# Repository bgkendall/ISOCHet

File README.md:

# ISOCHět

Macro pad based around an ISO Enter and using the CH552E MCU.

## Prerequisites

 * KiCad v7.0.9 or later
 * The following KiCad plugins are used for keyboard-specific components:
   * [marbastlib](https://github.com/ebastler/marbastlib) — footprints
   * [Keyswitch Kicad Library](https://github.com/kiswitch/kiswitch) —  3D models
 * [Josefin Sans](https://github.com/googlefonts/josefinsans) font — used for PCB text
 * FreeCAD v0.21.2 or later

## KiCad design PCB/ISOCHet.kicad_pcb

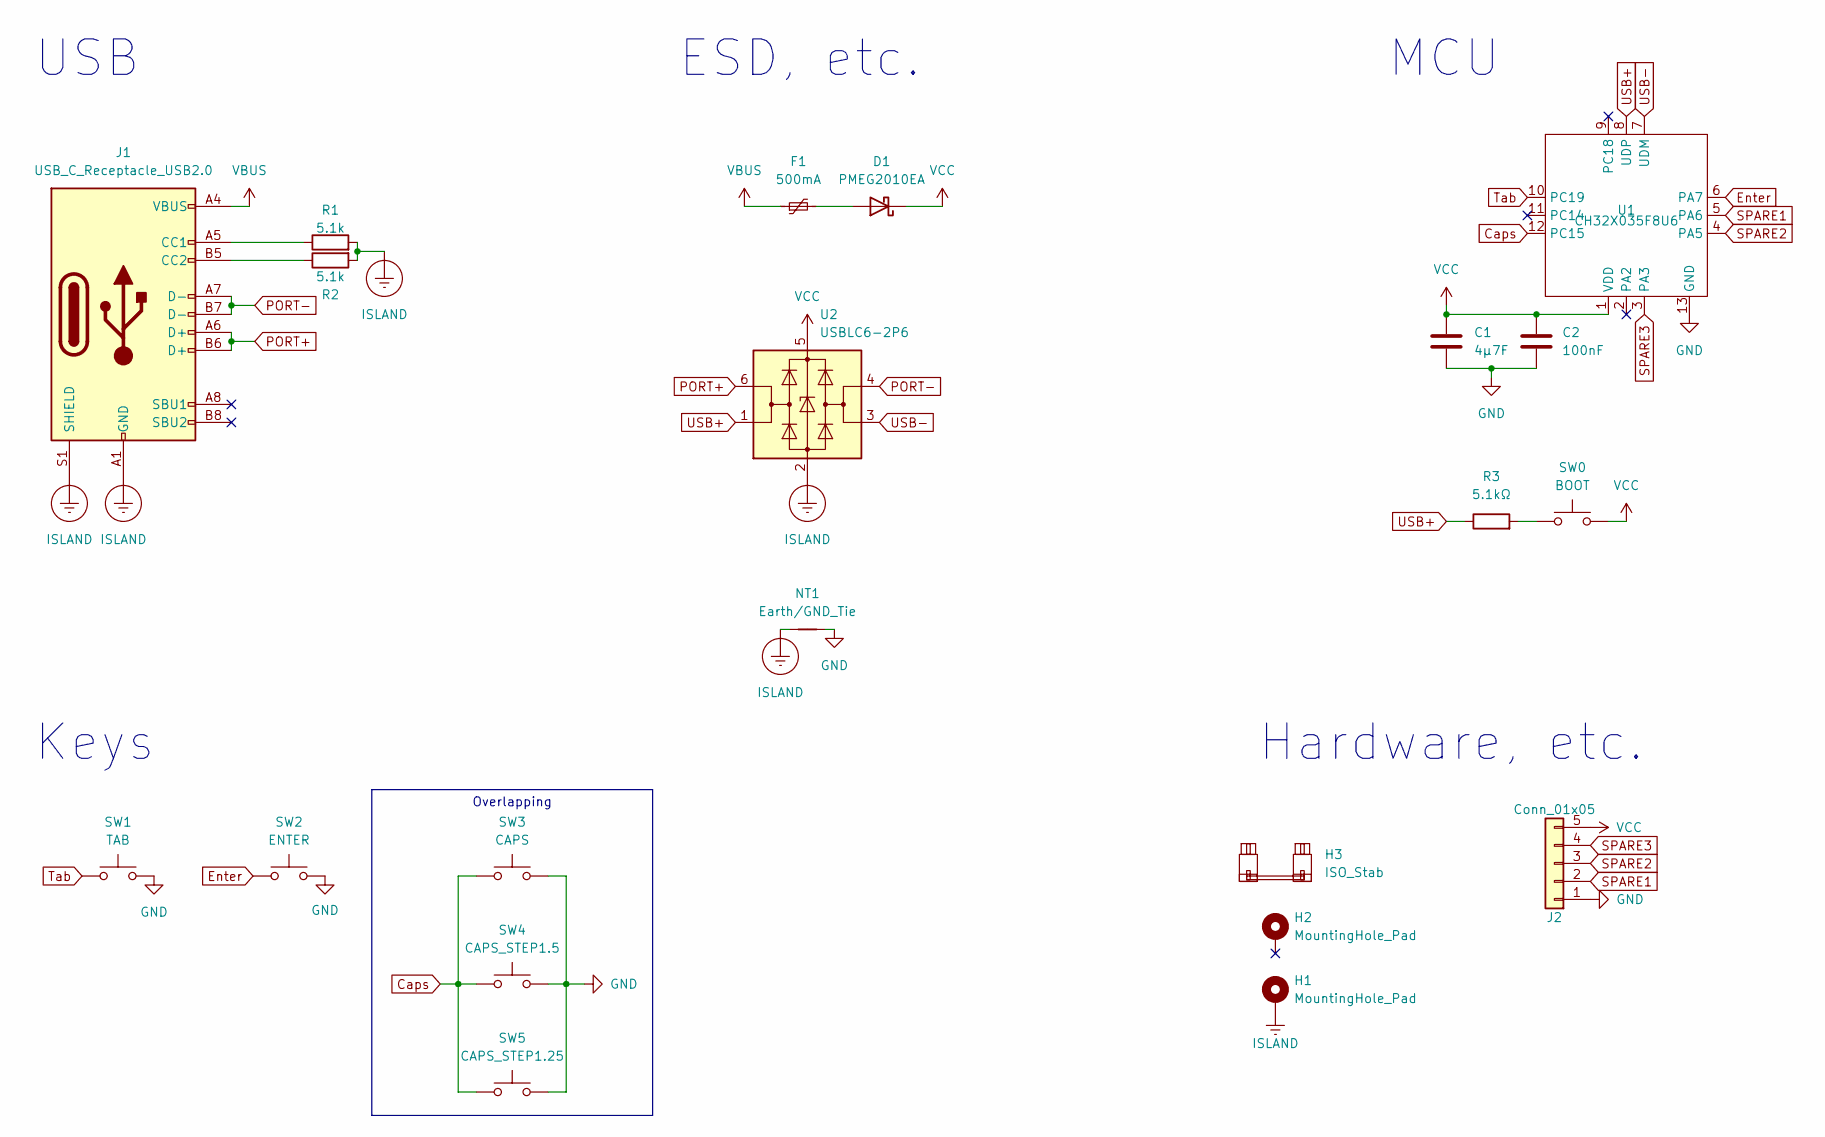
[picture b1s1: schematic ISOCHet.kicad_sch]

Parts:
C1: 4µ7F; C_0603_1608Metric_Pad1.08x0.95mm_HandSolder; LCSC C66501
C2: 100nF; C_0603_1608Metric_Pad1.08x0.95mm_HandSolder; LCSC C66501
D1: PMEG2010EA; D_SOD-323; LCSC C2837790
F1: 500mA; Fuse_0603_1608Metric_Pad1.05x0.95mm_HandSolder; LCSC C210357
H1, H2: MountingHole_Pad; MountingHole_2.2mm_M2_DIN965_Pad
H3: ISO_Stab; STAB_MX_P_ISO-ROT
J1: USB_C_Receptacle_USB2.0; GSB1C211110DS1HR; LCSC C2840393
J2: Conn_01x05; PinHeader_1x05_P2.00mm_Vertical
NT1: Earth/GND_Tie; NetTie_Via
R1, R2: 5.1k; R_0603_1608Metric_Pad0.98x0.95mm_HandSolder; LCSC C23186
R3: 5.1kΩ; R_0603_1608Metric_Pad0.98x0.95mm_HandSolder; LCSC C25804
SW0: BOOT; SW_SPST_SKQG_WithStem; LCSC C115351
SW1: TAB; SW_MX_1.5u
SW2: ENTER; SW_MX_1u
SW3: CAPS; SW_MX_1.75u
SW4: CAPS_STEP1.5; SW_MX_1.75u_STP_1.5
SW5: CAPS_STEP1.25; SW_MX_1.75u_STP_1.25
U1: CH32X035F8U6; UQFN-12-1EP_2x2mm_P0.4mm_EP1.1x1.1mm
U2: USBLC6-2P6; SOT-23-6_Handsoldering; LCSC C2827654

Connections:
Caps: SW3.1, SW4.1, SW5.1, U1.12 (PC15)
Enter: SW2.1, U1.6 (PA7)
GND: C1.2, C2.1, J2.1, NT1.2, SW1.2, SW2.2, SW3.2, SW4.2, SW5.2, U1.13 (GND)
ISLAND: H1.1 (1_1), J1.A1 (GND), J1.A12 (GND), J1.B1 (GND), J1.B12 (GND), J1.S1 (SHIELD), NT1.1, R1.2, R2.2, U2.2 (GND)
unnamed: D1.2 (A), F1.2
unnamed: J1.A5 (CC1), R1.1
unnamed: J1.B5 (CC2), R2.1
unnamed: R3.2, SW0.2
PORT+: J1.A6 (D+), J1.B6 (D+), U2.6 (I/O1)
PORT-: J1.A7 (D-), J1.B7 (D-), U2.4 (I/O2)
SPARE1: J2.2, U1.5 (PA6)
SPARE2: J2.3, U1.4 (PA5)
SPARE3: J2.4, U1.3 (PA3)
Tab: SW1.1, U1.10 (PC19)
USB+: R3.1, U1.8 (UDP), U2.1 (I/O1)
USB-: U1.7 (UDM), U2.3 (I/O2)
VBUS: F1.1, J1.A4 (VBUS), J1.A9 (VBUS), J1.B4 (VBUS), J1.B9 (VBUS)
VCC: C1.1, C2.2, D1.1 (K), J2.5, SW0.1, U1.1 (VDD), U2.5 (VBUS)

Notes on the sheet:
Keys
MCU
Hardware, etc.
ESD, etc.
USB
Overlapping

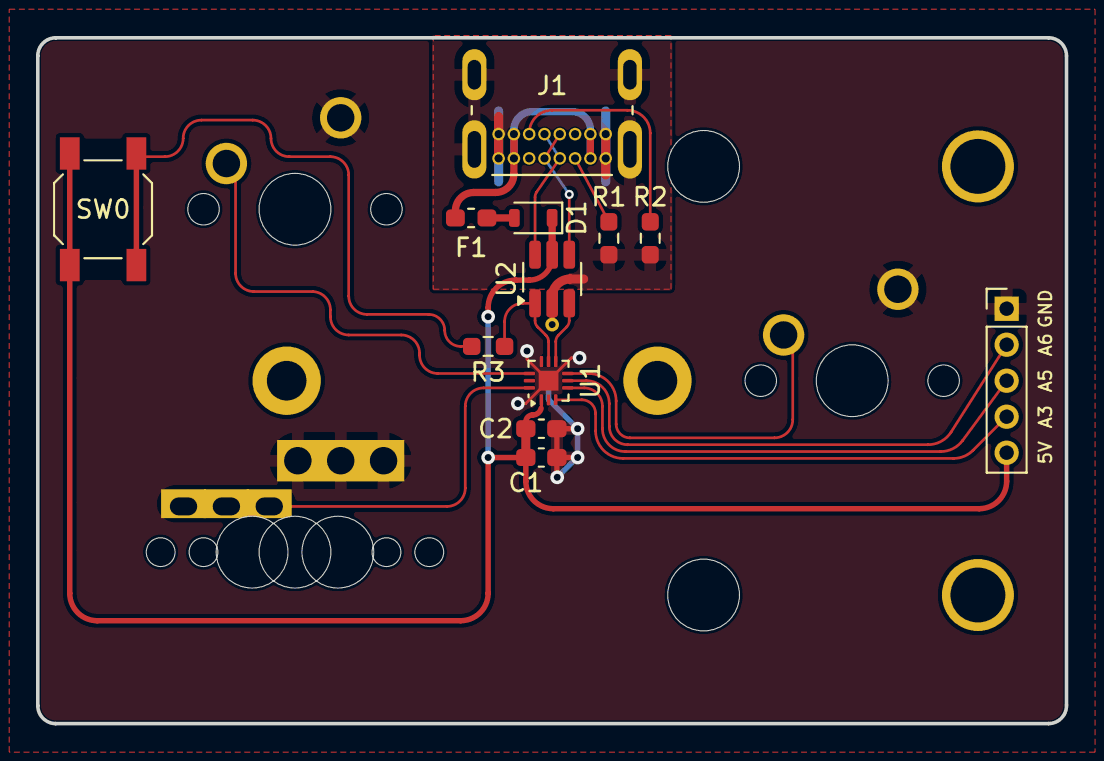
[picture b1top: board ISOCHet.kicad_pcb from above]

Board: 2 copper layers, 57.1 x 38.1 mm, 21 parts (0 on the bottom side), 18 nets.

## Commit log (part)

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2024-04-15 Create LICENSE
2024-04-16 Add first version of ISOCHet PCB
2024-04-16 Flip USB port to top side; add 3D models
2024-04-17 Add LSCC part numbers; add 3D models for MX switches and stabiliser
2024-04-17 Move OSHW logo to front, PCB name, etc. to back, and straighten a few traces
2024-04-17 Swap R1 and R2
    There’s more room for the via on the other side of the USB port.
2024-04-21 Rotate ISO stabiliser, improve STEP export
2024-04-21 Add first draft of case
2024-04-21 Move CC resistors away from PCB edge
2024-04-21 Add cutouts for USB port solder
2024-04-21 Remove local copy of switch models — use plugin instead
2024-04-21 Move components
    * Move decoupling capacitor C1 close to U1
    * Move U1 away from PCB edge
    * Align U1 with PCB centreline
2024-04-21 Added prerequisites section to README
2024-04-22 Create ISOCHet logo
2024-04-22 Use larger footprint for J2 header
2024-04-22 Update PCB model in case design
2024-04-22 Tweak ESD routing
2024-04-23 Use Alps SKQG switch for BOOT, update LCSC part numbers, add DigiKey part numbers
2024-04-23 Change footprint for USB port
    USB C socket is now GSB1C211110DS1HR instead of GCT USB4085. Update routing with more filleting on 90° corners.
2024-04-23 Swap R1 and R2 (again)
    Also, make some routing prettier.
2024-04-25 Tidy up schematic
2024-04-25 Refresh from schematic and tweak routing
2024-04-25 Rotated CH552 90° and rerouted accordingly
2024-04-26 Change routing of UDM and UDP
    Now leave U2 straight down rather than at 90°
2024-04-26 Tweak silkscreen lables for R3, C1 and C2
2024-04-26 Match width of pin-to-pin and thermal relief connections on Caps and J2
2024-04-26 Scooch order number
2024-04-26 Add courtyard for stabiliser screw pads
2024-04-26 Update 3D model of PCB
2024-04-26 Tweak position of USB port, update PCB model in case design
2024-04-29 Create draft of version using CH552E
2024-05-02 Correct CH552E symbol
2024-05-02 Move all components to front
    USB data pins on port now line up with CH552E and do not need to crossover.
    R1 and R2 remain on back.
    Tweaked overlapping Caps Lock switch footprints to reduce DRC errors.
    Power tracks are now 0.3mm to match maximum width of CH552E pads.
2024-05-02 Use Josefin Sans for all mask text
2024-05-03 Prepare for production
    * Set fabrication flags.
    * Remove order number — cost is no different for a board this small.
2024-05-03 Isolate USD port ground from main PCB ground
2024-05-03 Move CC1 such that it is before U1, not after
2024-05-03 Round outside corners of keep-out areas
    KiCad only seems to round the inside corners, so some arcs on the GND net are added.
2024-05-03 Reroute UDP to Boot switch tracks
2024-05-03 Relocate and enlarge logo
2024-05-04 Switch USBLC6 (U2) to cheaper LCSC part number
2024-05-06 Update PCB 3D model
2024-05-07 Recreate case design using length settings from spreadsheet
2024-05-07 Add support for multiple standoffs
    Specifying a standoff X and/or Y offset in the spreadsheet will cause additional standoffs to be mirrored.
    Also, add appropriate labels to pads, pockets, etc.
2024-05-08 Change R3 footprint to combined THT/SMD
    I realised I had a bunch of DIN0207 axial 10kΩ resistors, so switched the footprint for R3 to support *either* through hole *or* surface mount. I looked at doing the same for R1 and R2, but fitting a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
    Also fixed a DRC error on the VCC line into U1.
2024-05-10 Redo isolated ground
    Removed keep-out zones between parts of GND plane. Instead, moved USB port to “Earth” net and added a “jumper” between Earth and GND. The jumper is a simple custom footprint with three pairs of overl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
    R1 and R2 have been relocated to above and below the USB port’s pins rather than being left and right of the port. This simplifies their routing.
2024-05-10 Refresh PCB 3D model to check new R1 and R2 locations
2024-05-10 Connect USBLC6 to isolated ground
    The USB ground (“Earth”) zone extends further down the board and the U2 ground pin connects to it and to H1 (the central mounting hole). H1 now has two pins and serves as the bridge between the two g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
    Also:
    * Switch U2 to more accurate USBLC6-2**SC6**
    * Remove all silkscreen from back except “R1” and “R2”
2024-05-10 Update U1 silkscreen position to match U2
    I.e., next to pin 1
2024-05-12 Change standoff hole to 1.6mm diameter to match M2 tap
    See https://www.aliexpress.us/item/3256801225285833.html
2024-05-18 Make cosmetic tweaks to USB port ground plane
2024-05-18 Update CH552E symbol
2024-05-21 Fix DRC error
2024-05-21 Generate Gerbers
2024-05-22 Export STF models of case parts
2024-06-08 Migrate project to KiCad v8
2024-06-08 Fix missing BOOT label; update PCB from v8 schematic
2024-06-08 Add ground stitching vias around MCU
2024-06-08 Add gap for ground plane between boot and switch traces
2024-06-09 Decrease diameter of MX switch mounting pins
    The diameter has been decreased from 1.75mm to 1.6mm. This should improve the alignment of the switches given the plateless design of the case. However, some switches may no longer fit.
2024-06-09 Increase pad size on north side of Caps pin 1
2024-06-12 Increase gap between boot and switch traces
2024-06-17 Move R1 & R2 to top of board
2024-06-18 Experiment with surface mount USB C socket
2024-06-18 Further tweaks to USB routing
2024-06-19 Fix project symbol library and CH552 symbol names
2025-12-12 Update KiCad version
